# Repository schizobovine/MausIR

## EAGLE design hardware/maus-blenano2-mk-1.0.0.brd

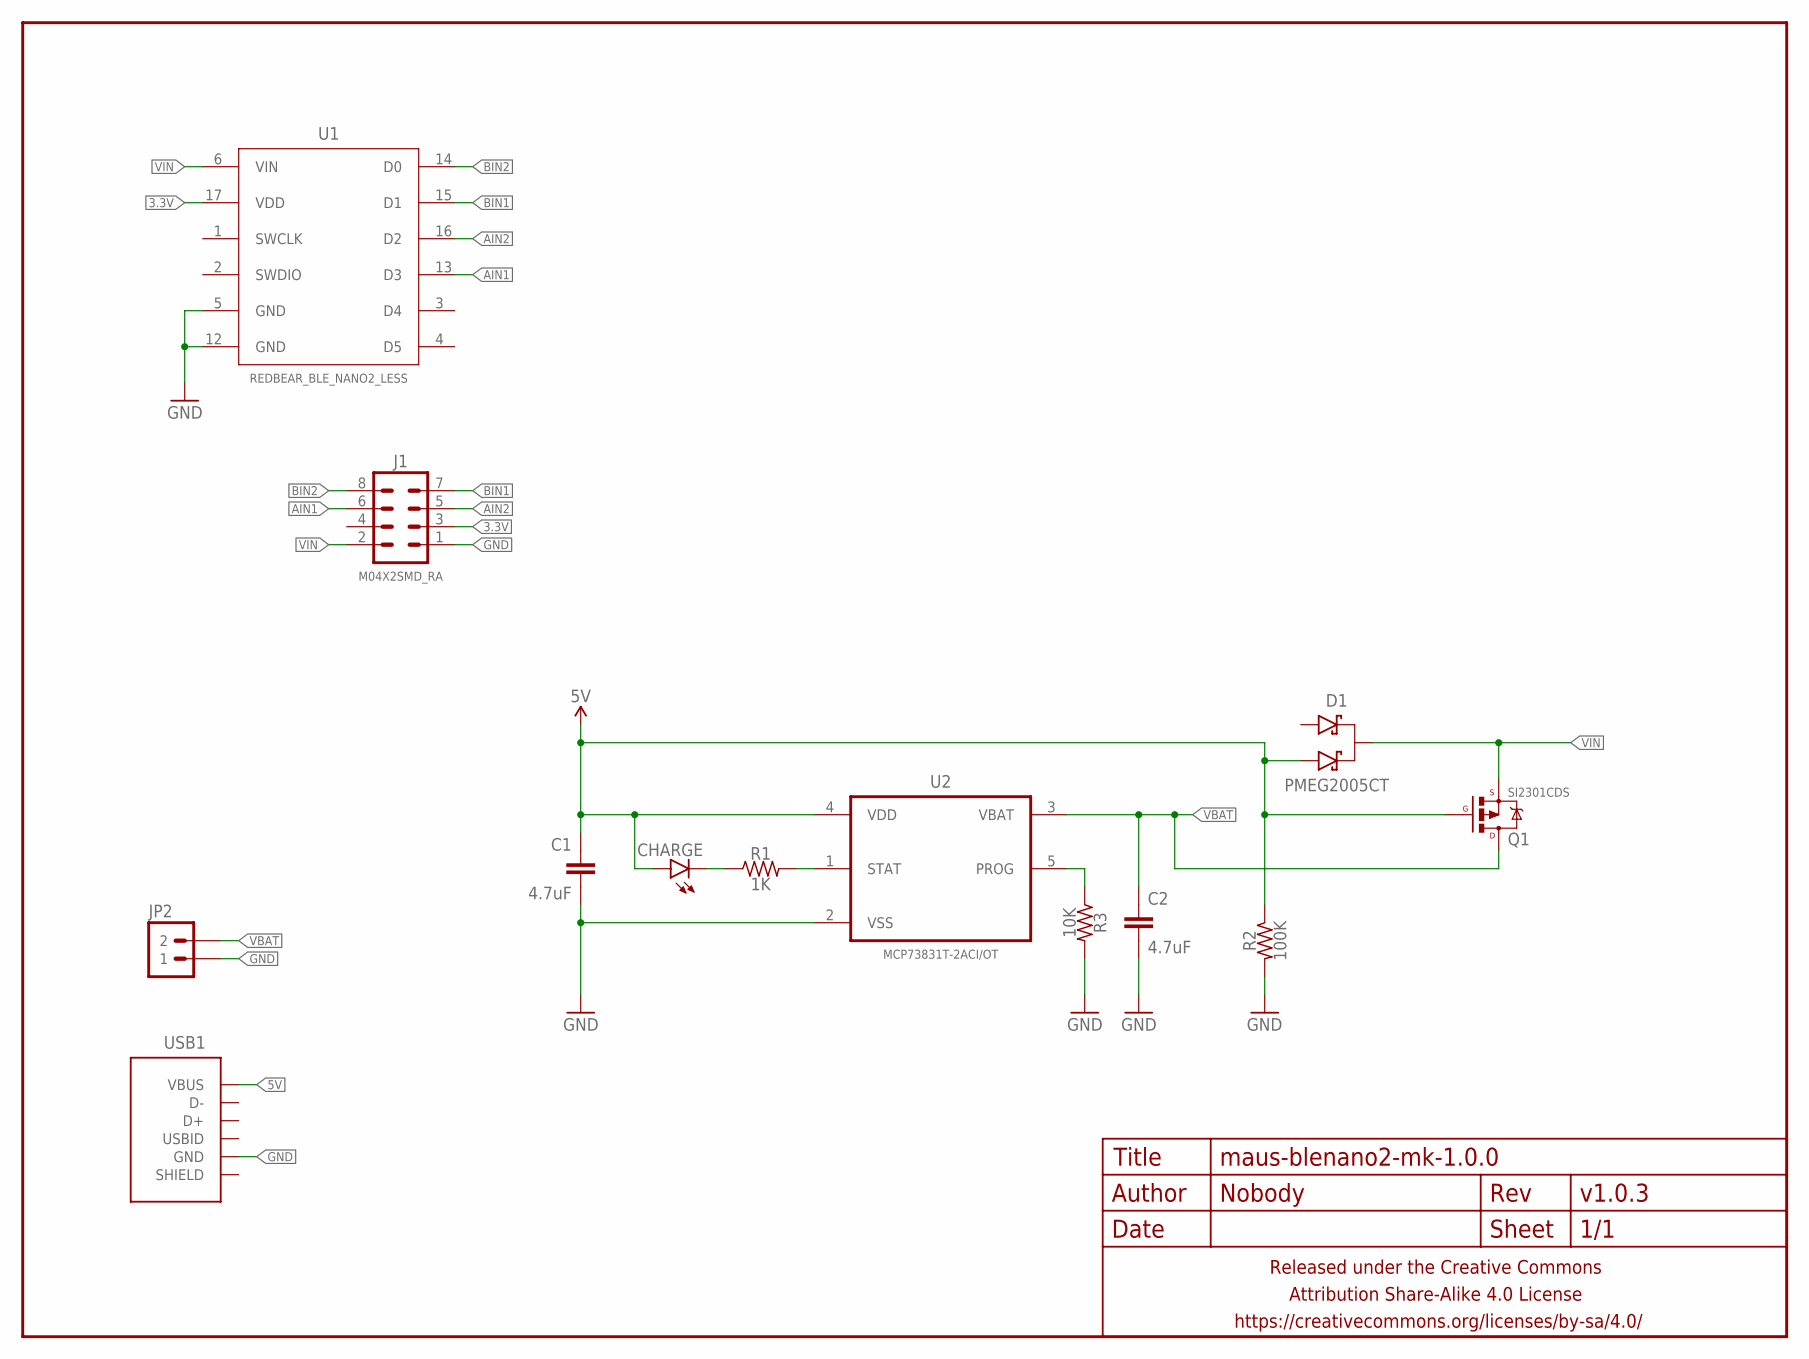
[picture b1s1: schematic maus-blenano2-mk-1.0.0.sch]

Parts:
C1, C2: 4.7uF; C0603-TIGHTER
CHARGE: LED0603-TIGHT; LED-0603-TIGHT
D1: PMEG2005CT; SOT23
FRAME1: FRAME-LETTERNO_PACKAGE; DUMMY
J1: M04X2SMD_RA; 2X4_SMD_RA
JP2: M02JST-SH-VERT; JST-2-SH-VERT
Q1: SI2301CDS; SOT23
R1: 1K; R0603-TIGHTER
R2: 100K; R0603-TIGHTER
R3: 10K; R0603-TIGHTER
U1: REDBEAR_BLE_NANO2_LESS
U2: MCP73831T-2ACI/OT; SOT95P280X145-5N
USB1: USB-AB-SHIELDZX80-B-5P_VERTICAL_SMD; ZX80-B-5P-30

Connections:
3.3V: J1.3, U1.17 (VDD)
5V: C1.1, CHARGE.A, D1.2 (A2), Q1.1 (G), R2.1, U2.4 (VDD), USB1.5 (VBUS)
AIN1: J1.6, U1.13 (D3)
AIN2: J1.5, U1.16 (D2)
BIN1: J1.7, U1.15 (D1)
BIN2: J1.8, U1.14 (D0)
GND: C1.2, C2.2, J1.1, JP2.1, R2.2, R3.2, U1.5 (GND), U1.12 (GND), U2.2 (VSS), USB1.1 (GND)
unnamed: R1.2, U2.1 (STAT)
unnamed: CHARGE.C, R1.1
unnamed: R3.1, U2.5 (PROG)
VBAT: C2.1, JP2.2, Q1.3 (D), U2.3 (VBAT)
VIN: D1.3 (K), J1.2, Q1.2 (S), U1.6 (VIN)

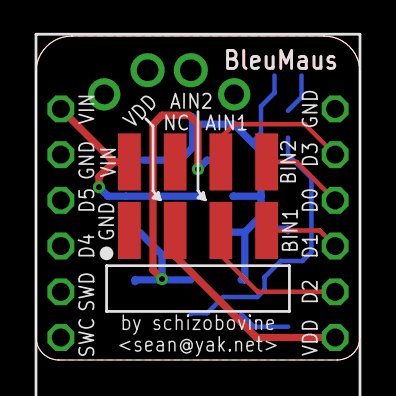
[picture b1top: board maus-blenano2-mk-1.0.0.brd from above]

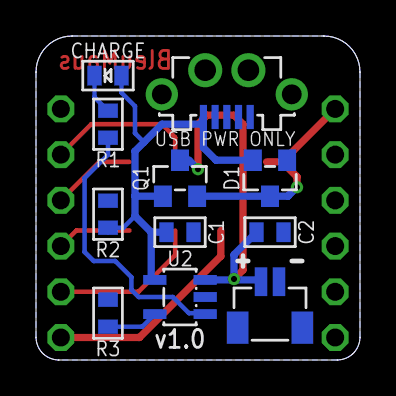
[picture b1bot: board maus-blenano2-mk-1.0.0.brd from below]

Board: 2 copper layers, 18.0 x 18.0 mm, 14 parts (11 on the bottom side), 12 nets.

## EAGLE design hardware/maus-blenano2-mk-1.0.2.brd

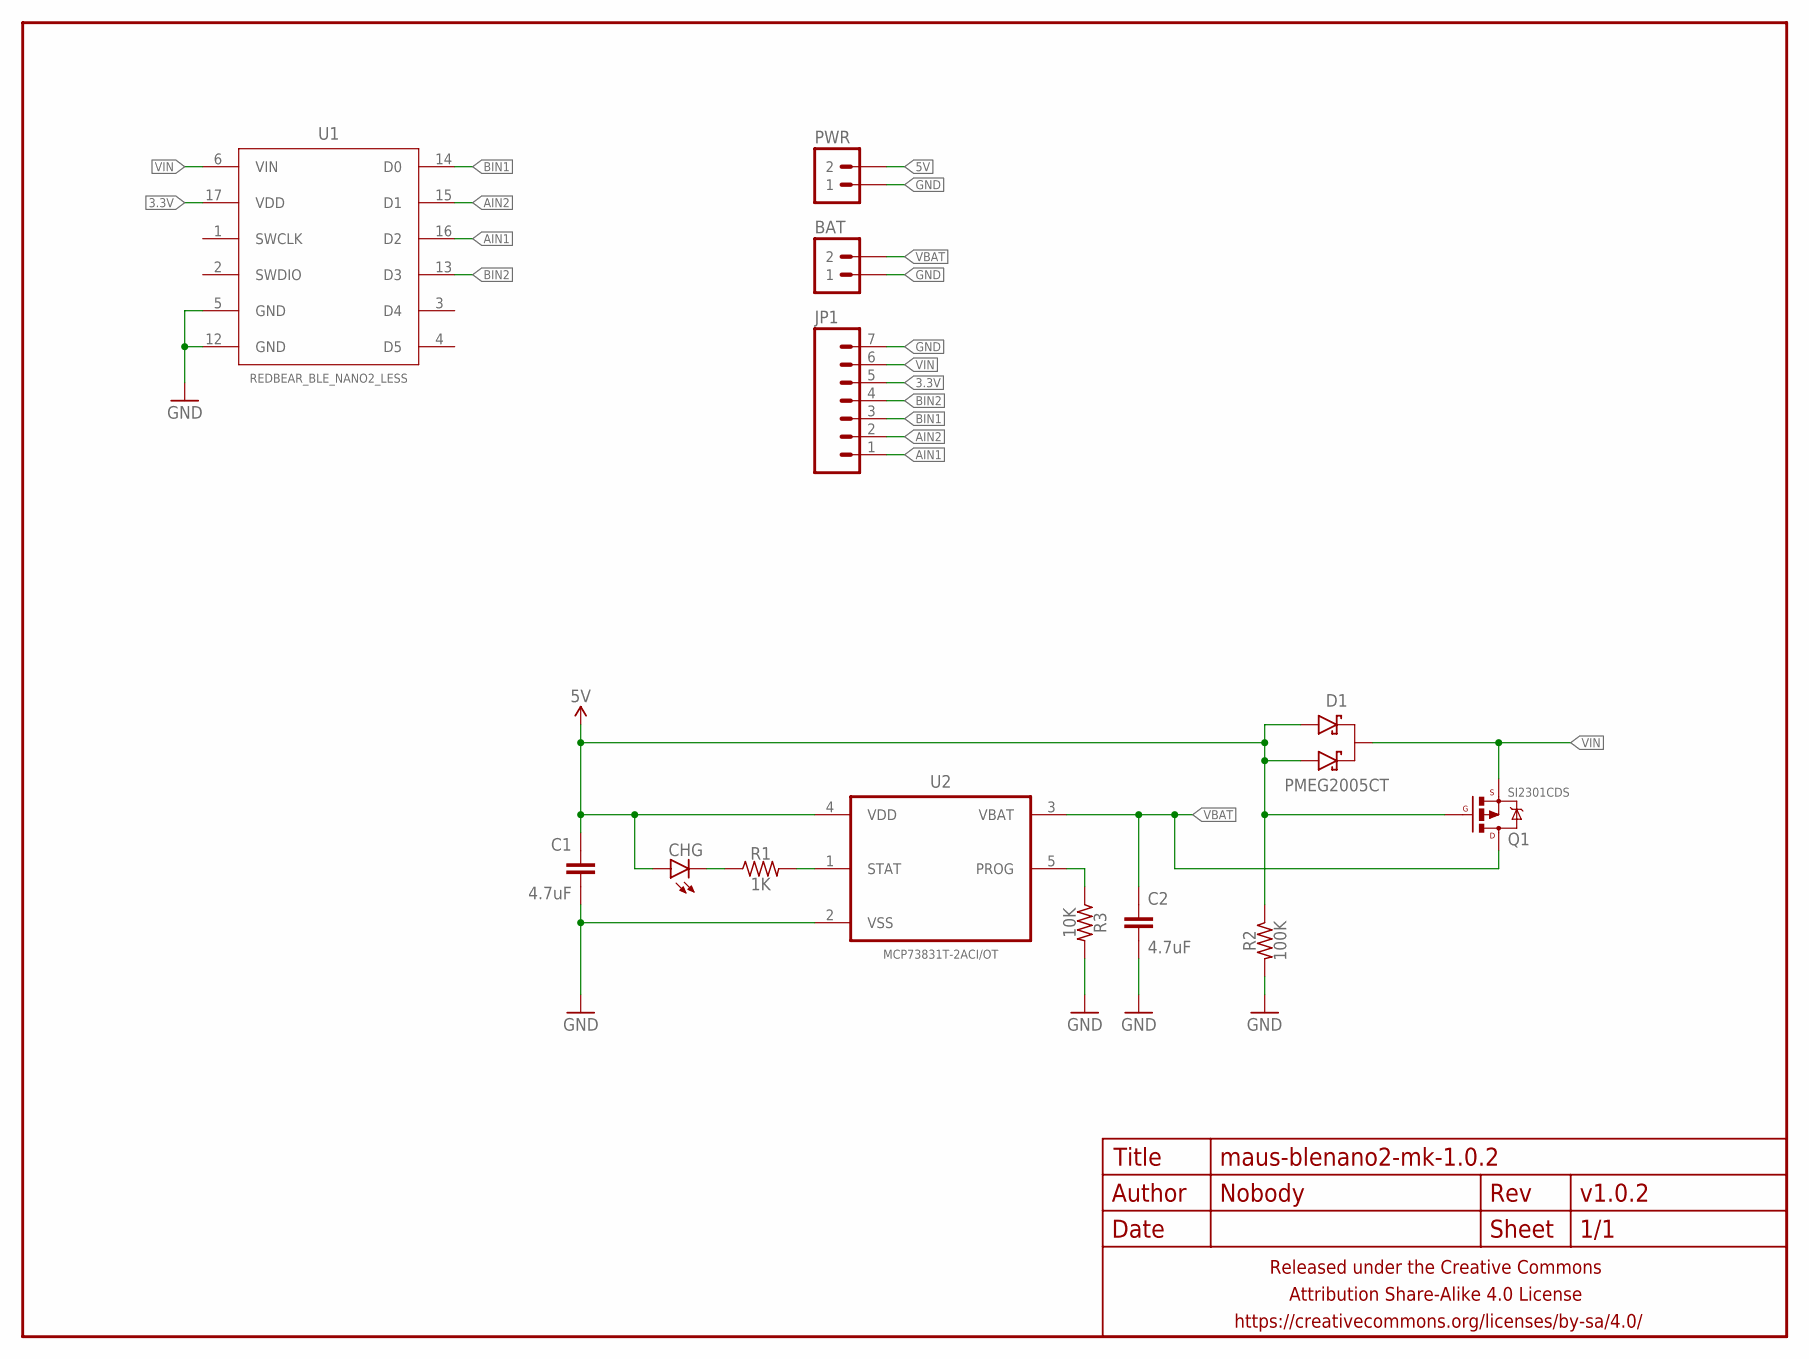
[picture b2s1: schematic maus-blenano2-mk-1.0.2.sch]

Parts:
BAT: M02JST-SH-RA; JST-2-SH-RA
C1, C2: 4.7uF; C0603-TIGHTER
CHG: LED0603-TIGHT; LED-0603-TIGHT
D1: PMEG2005CT; SOT23
FRAME1: FRAME-LETTERNO_PACKAGE; DUMMY
JP1: M07PTH-CENTERED; 1X07_CENTERED
PWR: M02JST-SH-RA; JST-2-SH-RA
Q1: SI2301CDS; SOT23
R1: 1K; R0603-TIGHTER
R2: 100K; R0603-TIGHTER
R3: 10K; R0603-TIGHTER
U1: REDBEAR_BLE_NANO2_LESS
U2: MCP73831T-2ACI/OT; SOT95P280X145-5N

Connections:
3.3V: JP1.5, U1.17 (VDD)
5V: C1.1, CHG.A, D1.1 (A1), D1.2 (A2), PWR.2, Q1.1 (G), R2.1, U2.4 (VDD)
AIN1: JP1.1, U1.16 (D2)
AIN2: JP1.2, U1.15 (D1)
BIN1: JP1.3, U1.14 (D0)
BIN2: JP1.4, U1.13 (D3)
GND: BAT.1, C1.2, C2.2, JP1.7, PWR.1, R2.2, R3.2, U1.5 (GND), U1.12 (GND), U2.2 (VSS)
unnamed: R1.2, U2.1 (STAT)
unnamed: CHG.C, R1.1
unnamed: R3.1, U2.5 (PROG)
VBAT: BAT.2, C2.1, Q1.3 (D), U2.3 (VBAT)
VIN: D1.3 (K), JP1.6, Q1.2 (S), U1.6 (VIN)

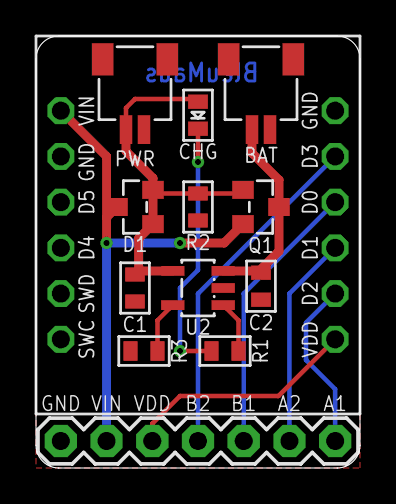
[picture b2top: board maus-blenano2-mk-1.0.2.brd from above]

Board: 2 copper layers, 18.0 x 24.0 mm, 14 parts (0 on the bottom side), 12 nets.

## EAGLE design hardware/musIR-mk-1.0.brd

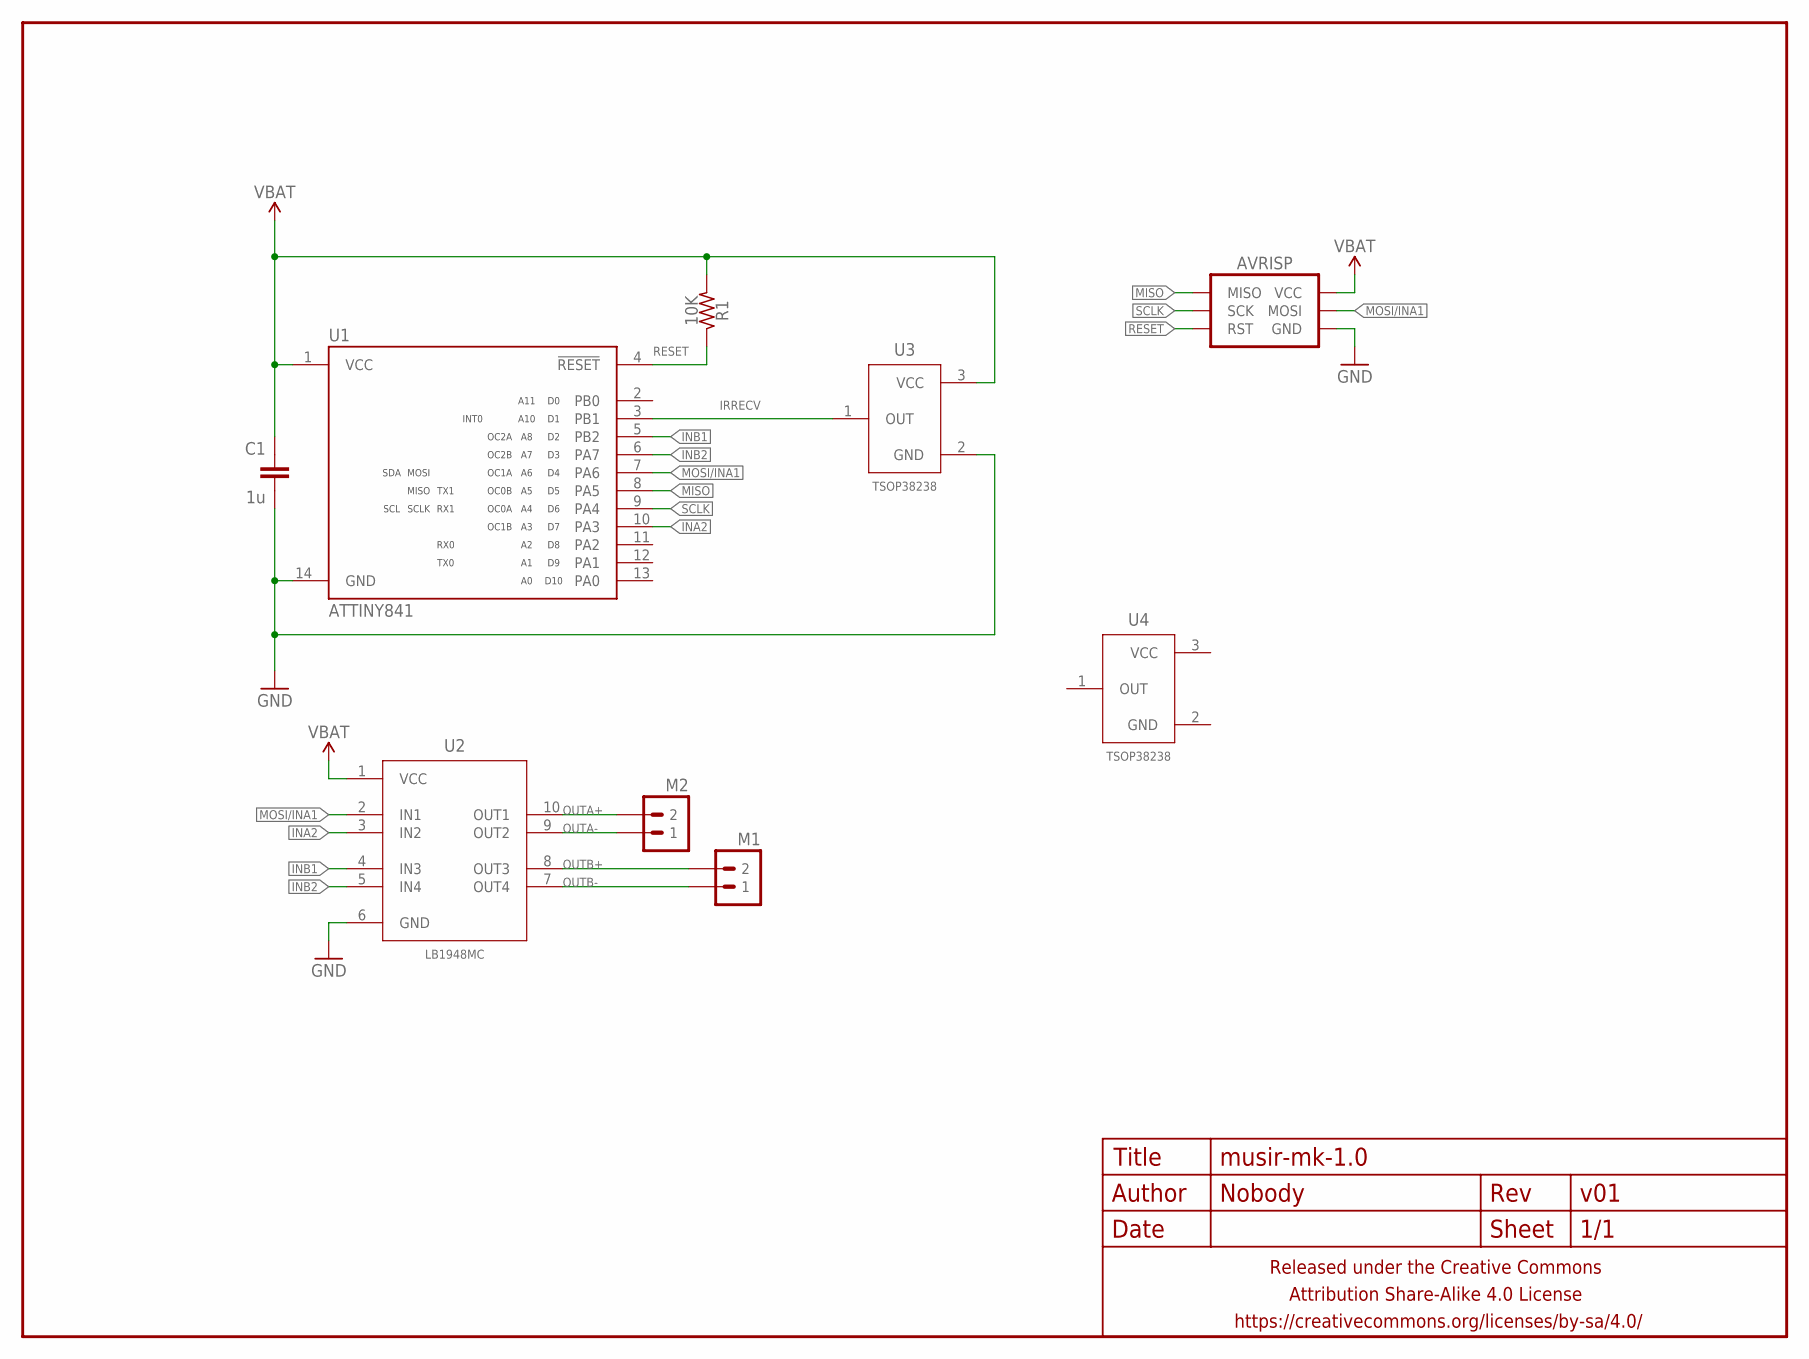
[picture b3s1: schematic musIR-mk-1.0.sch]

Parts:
AVRISP: AVR_SPI_PRG_6TESTPOINTS; 2X3_TEST_POINTS
C1: 1u; C0603-TIGHTER
FRAME1: FRAME-LETTERNO_PACKAGE; DUMMY
M1, M2: M02PTH; 1X02
R1: 10K; R0603-TIGHTER
U1: ATTINY841; SO14
U2: LB1948MC; SO10-NOTREALLY
U3, U4: TSOP38238

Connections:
GND: AVRISP.6 (GND), C1.2, U1.14 (GND), U2.6 (GND), U3.2 (GND)
INA2: U1.10 (PA3), U2.3 (IN2)
INB1: U1.5 (PB2), U2.4 (IN3)
INB2: U1.6 (PA7), U2.5 (IN4)
IRRECV: U1.3 (PB1), U3.1 (OUT)
MISO: AVRISP.1 (MISO), U1.8 (PA5)
MOSI/INA1: AVRISP.4 (MOSI), U1.7 (PA6), U2.2 (IN1)
OUTA+: M2.2, U2.10 (OUT1)
OUTA-: M2.1, U2.9 (OUT2)
OUTB+: M1.2, U2.8 (OUT3)
OUTB-: M1.1, U2.7 (OUT4)
RESET: AVRISP.5 (RST), R1.1, U1.4 (!RESET)
SCLK: AVRISP.3 (SCK), U1.9 (PA4)
VBAT: AVRISP.2 (VCC), C1.1, R1.2, U1.1 (VCC), U2.1 (VCC), U3.3 (VCC)

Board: 2 copper layers, 10 parts (1 on the bottom side), 14 nets, no tracks yet.

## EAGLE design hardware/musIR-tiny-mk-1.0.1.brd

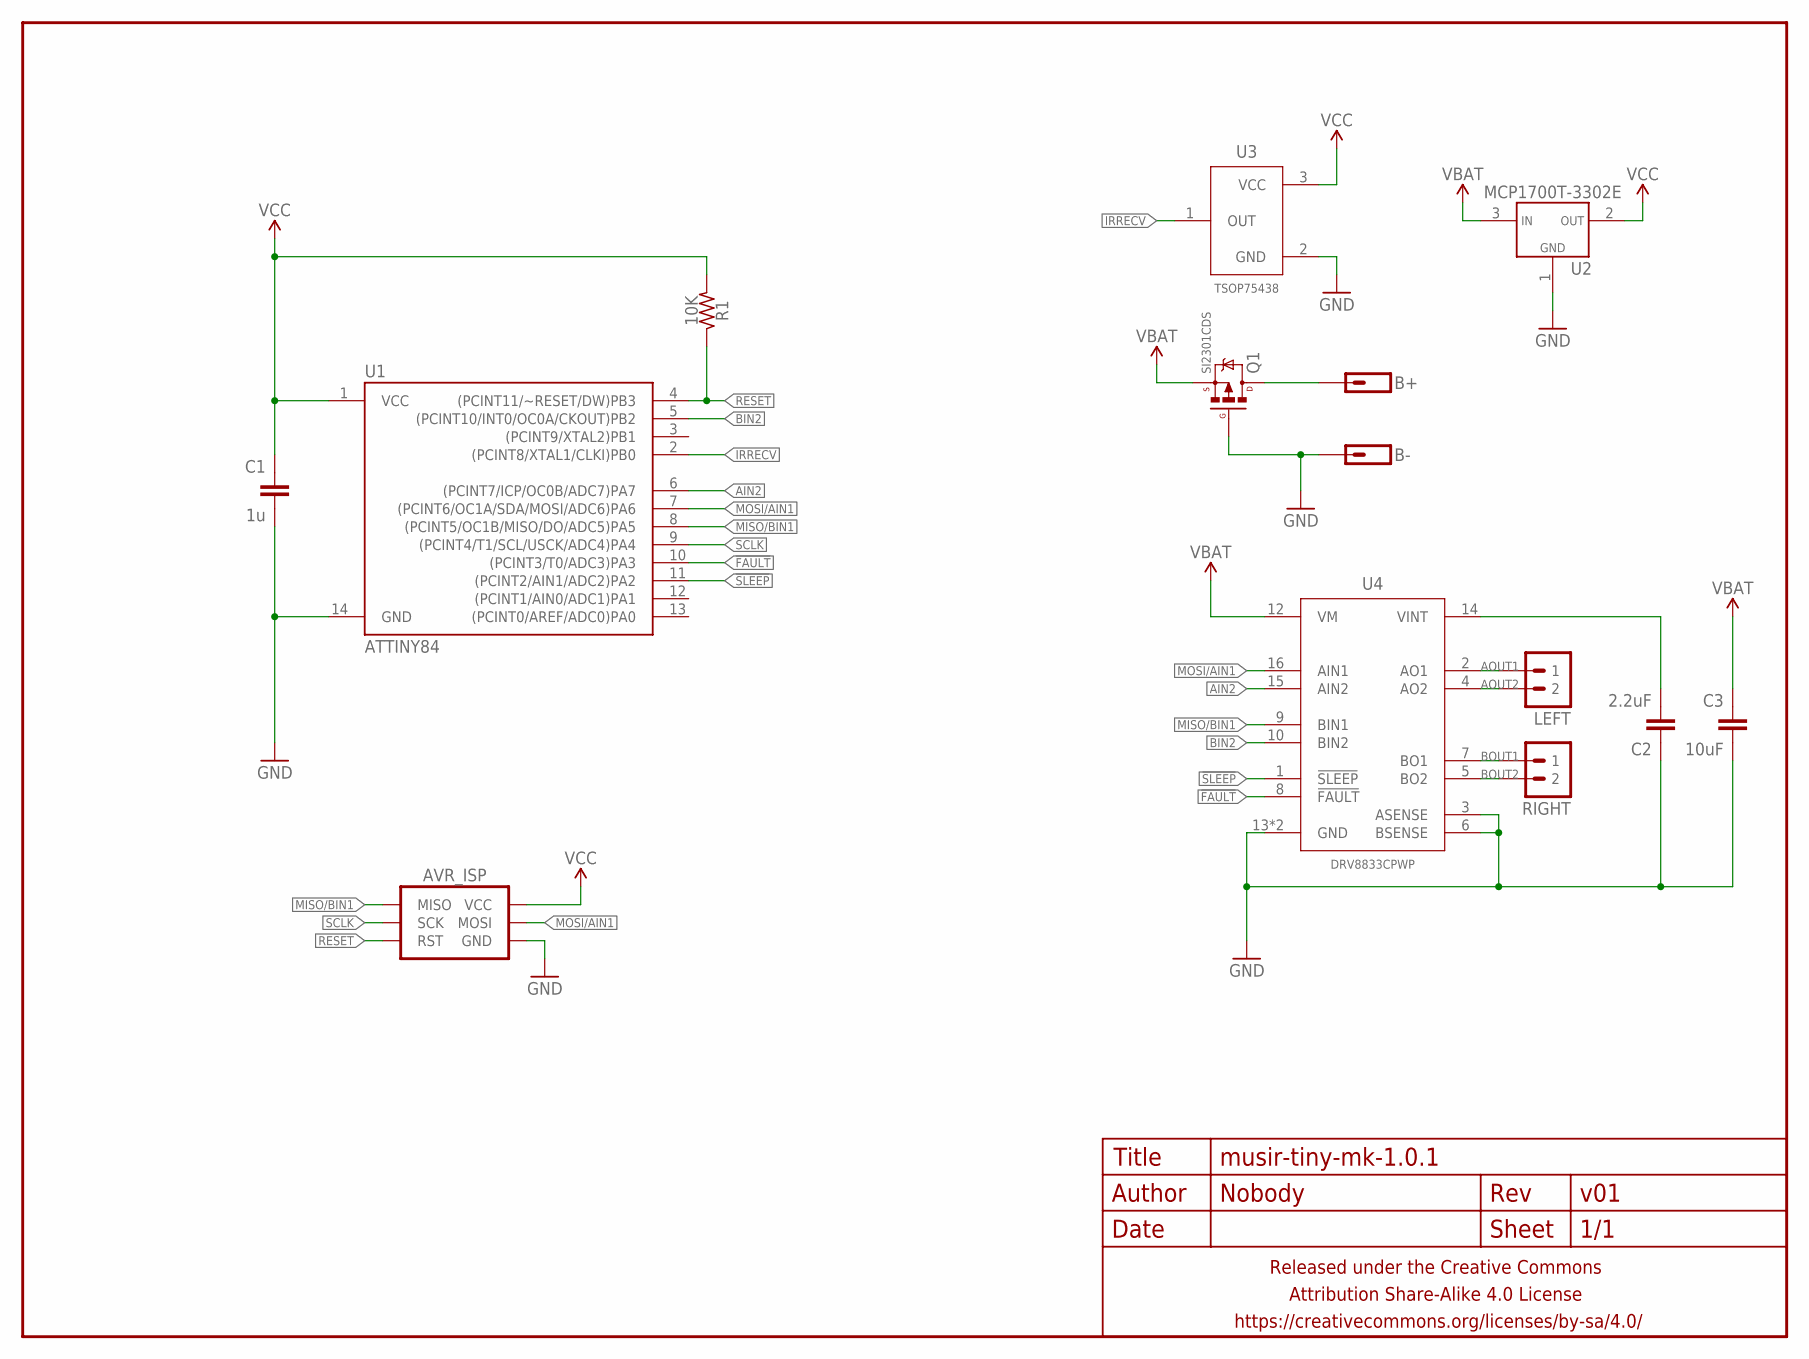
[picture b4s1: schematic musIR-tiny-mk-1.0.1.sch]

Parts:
AVR_ISP: AVR_SPI_PRG_6TESTPOINTS; 2X3_TEST_POINTS
B+: M01PTH; 1X01
B-: M01PTH; 1X01
C1: 1u; C0603-TIGHTER
C2: 2.2uF; C0603-TIGHTER
C3: 10uF; C0805-TIGHTER
FRAME1: FRAME-LETTERNO_PACKAGE; DUMMY
LEFT: M02PTH-CENTERED; 1X02-CENTER
Q1: SI2301CDS; SOT23
R1: 10K; R0402
RIGHT: M02PTH-CENTERED; 1X02-CENTER
U1: ATTINY84; SO14
U2: MCP1700T-3302E; SOT23-3
U3: TSOP75438; TSOP38238
U4: DRV8833CPWP; TSSOP-16-PAD

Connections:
!FAULT: U1.10 ((PCINT3/T0/ADC3)PA3), U4.8 (!FAULT)
!SLEEP: U1.11 ((PCINT2/AIN1/ADC2)PA2), U4.1 (!SLEEP)
AIN2: U1.6 ((PCINT7/ICP/OC0B/ADC7)PA7), U4.15 (AIN2)
AOUT1: LEFT.1, U4.2 (AO1)
AOUT2: LEFT.2, U4.4 (AO2)
BIN2: U1.5 ((PCINT10/INT0/OC0A/CKOUT)PB2), U4.10 (BIN2)
BOUT1: RIGHT.1, U4.7 (BO1)
BOUT2: RIGHT.2, U4.5 (BO2)
GND: AVR_ISP.6 (GND), B-.1, C1.2, C2.1, C3.2, Q1.1 (G), U1.14 (GND), U2.1 (GND), U3.2 (GND), U4.3 (ASENSE), U4.6 (BSENSE), U4.13 (GND), U4.PAD (GND)
IRRECV: U1.2 ((PCINT8/XTAL1/CLKI)PB0), U3.1 (OUT)
MISO/BIN1: AVR_ISP.1 (MISO), U1.8 ((PCINT5/OC1B/MISO/DO/ADC5)PA5), U4.9 (BIN1)
MOSI/AIN1: AVR_ISP.4 (MOSI), U1.7 ((PCINT6/OC1A/SDA/MOSI/ADC6)PA6), U4.16 (AIN1)
unnamed: B+.1, Q1.3 (D)
unnamed: C2.2, U4.14 (VINT)
RESET: AVR_ISP.5 (RST), R1.1, U1.4 ((PCINT11/~RESET/DW)PB3)
SCLK: AVR_ISP.3 (SCK), U1.9 ((PCINT4/T1/SCL/USCK/ADC4)PA4)
VBAT: C3.1, Q1.2 (S), U2.3 (VIN), U4.12 (VM)
VCC: AVR_ISP.2 (VCC), C1.1, R1.2, U1.1 (VCC), U2.2 (VOUT), U3.3 (VCC)

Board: 2 copper layers, 15 parts (4 on the bottom side), 18 nets, no tracks yet.

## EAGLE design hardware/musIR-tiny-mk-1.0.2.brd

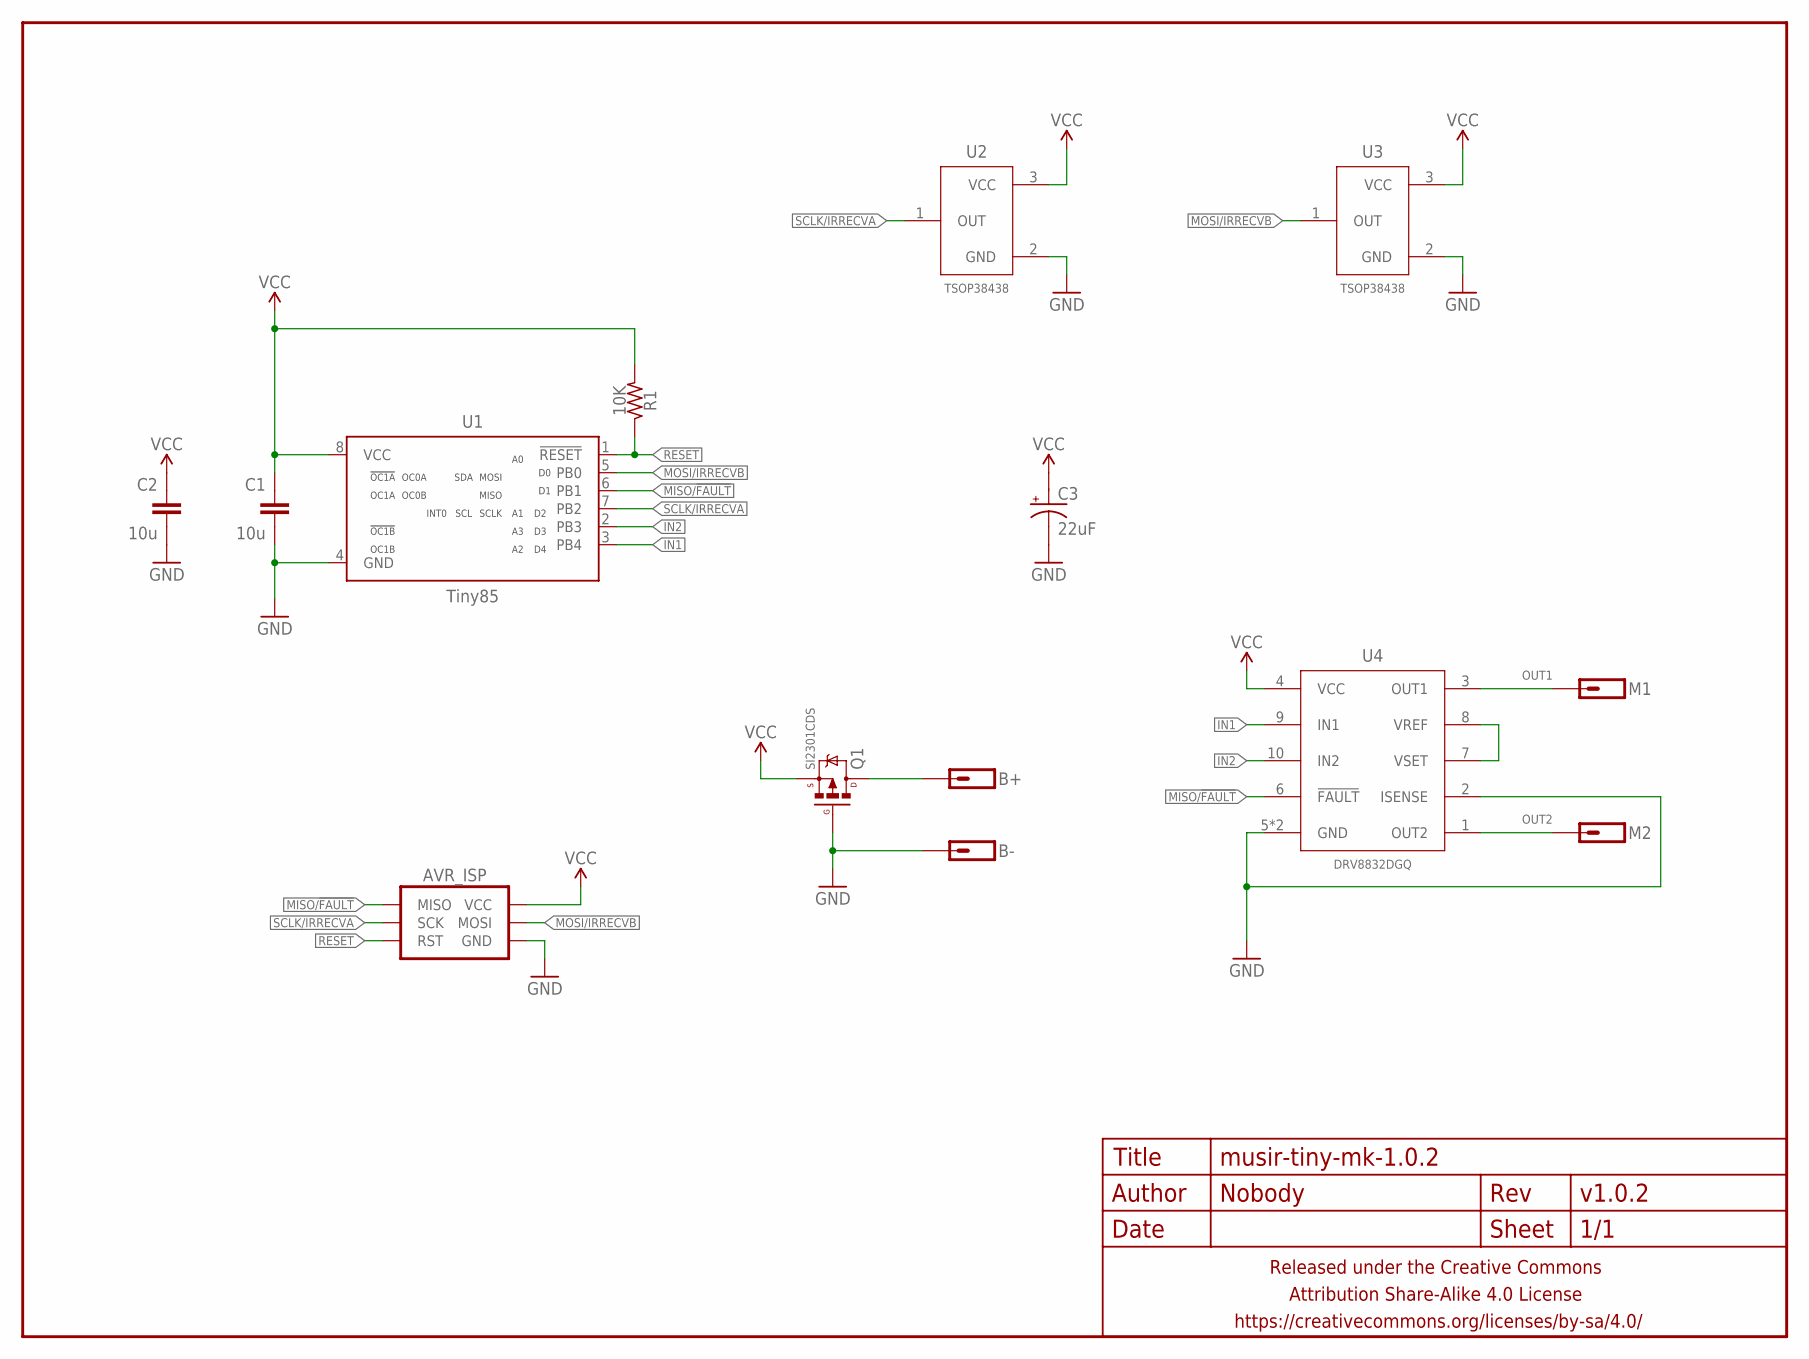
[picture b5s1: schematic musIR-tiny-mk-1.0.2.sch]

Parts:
AVR_ISP: AVR_SPI_PRG_6TESTPOINTS; 2X3_TEST_POINTS
B+: M01PTH; 1X01
B-: M01PTH; 1X01
C1, C2: 10u; C0805-TIGHTER
C3: 22uF; C/6032-28R
FRAME1: FRAME-LETTERNO_PACKAGE; DUMMY
M1, M2: M01PTH; 1X01
Q1: SI2301CDS; SOT23
R1: 10K; R0603-TIGHTER
U1: Tiny85; SO08-EIAJ
U2, U3: TSOP38438; TSOP38238
U4: DRV8832DGQ; MSOP-10-PAD

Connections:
GND: AVR_ISP.6 (GND), B-.1, C1.2, C2.2, C3.-, Q1.1 (G), U1.4 (GND), U2.2 (GND), U3.2 (GND), U4.2 (ISENSE), U4.5 (GND), U4.PAD (GND)
IN1: U1.3 (PB4), U4.9 (IN1)
IN2: U1.2 (PB3), U4.10 (IN2)
MISO/!FAULT: AVR_ISP.1 (MISO), U1.6 (PB1), U4.6 (!FAULT)
MOSI/IRRECVB: AVR_ISP.4 (MOSI), U1.5 (PB0), U3.1 (OUT)
unnamed: B+.1, Q1.3 (D)
unnamed: U4.7 (VSET), U4.8 (VREF)
OUT1: M1.1, U4.3 (OUT1)
OUT2: M2.1, U4.1 (OUT2)
RESET: AVR_ISP.5 (RST), R1.1, U1.1 (!RESET)
SCLK/IRRECVA: AVR_ISP.3 (SCK), U1.7 (PB2), U2.1 (OUT)
VCC: AVR_ISP.2 (VCC), C1.1, C2.1, C3.+, Q1.2 (S), R1.2, U1.8 (VCC), U2.3 (VCC), U3.3 (VCC), U4.4 (VCC)

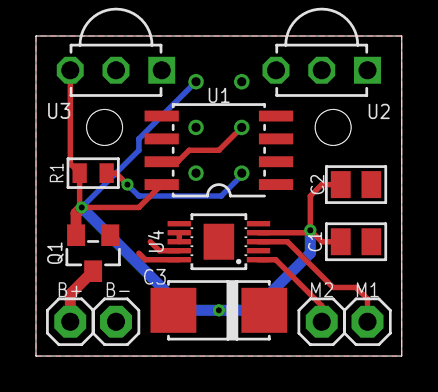
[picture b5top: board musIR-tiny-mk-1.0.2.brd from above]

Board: 2 copper layers, 20.3 x 17.8 mm, 15 parts (1 on the bottom side), 12 nets.

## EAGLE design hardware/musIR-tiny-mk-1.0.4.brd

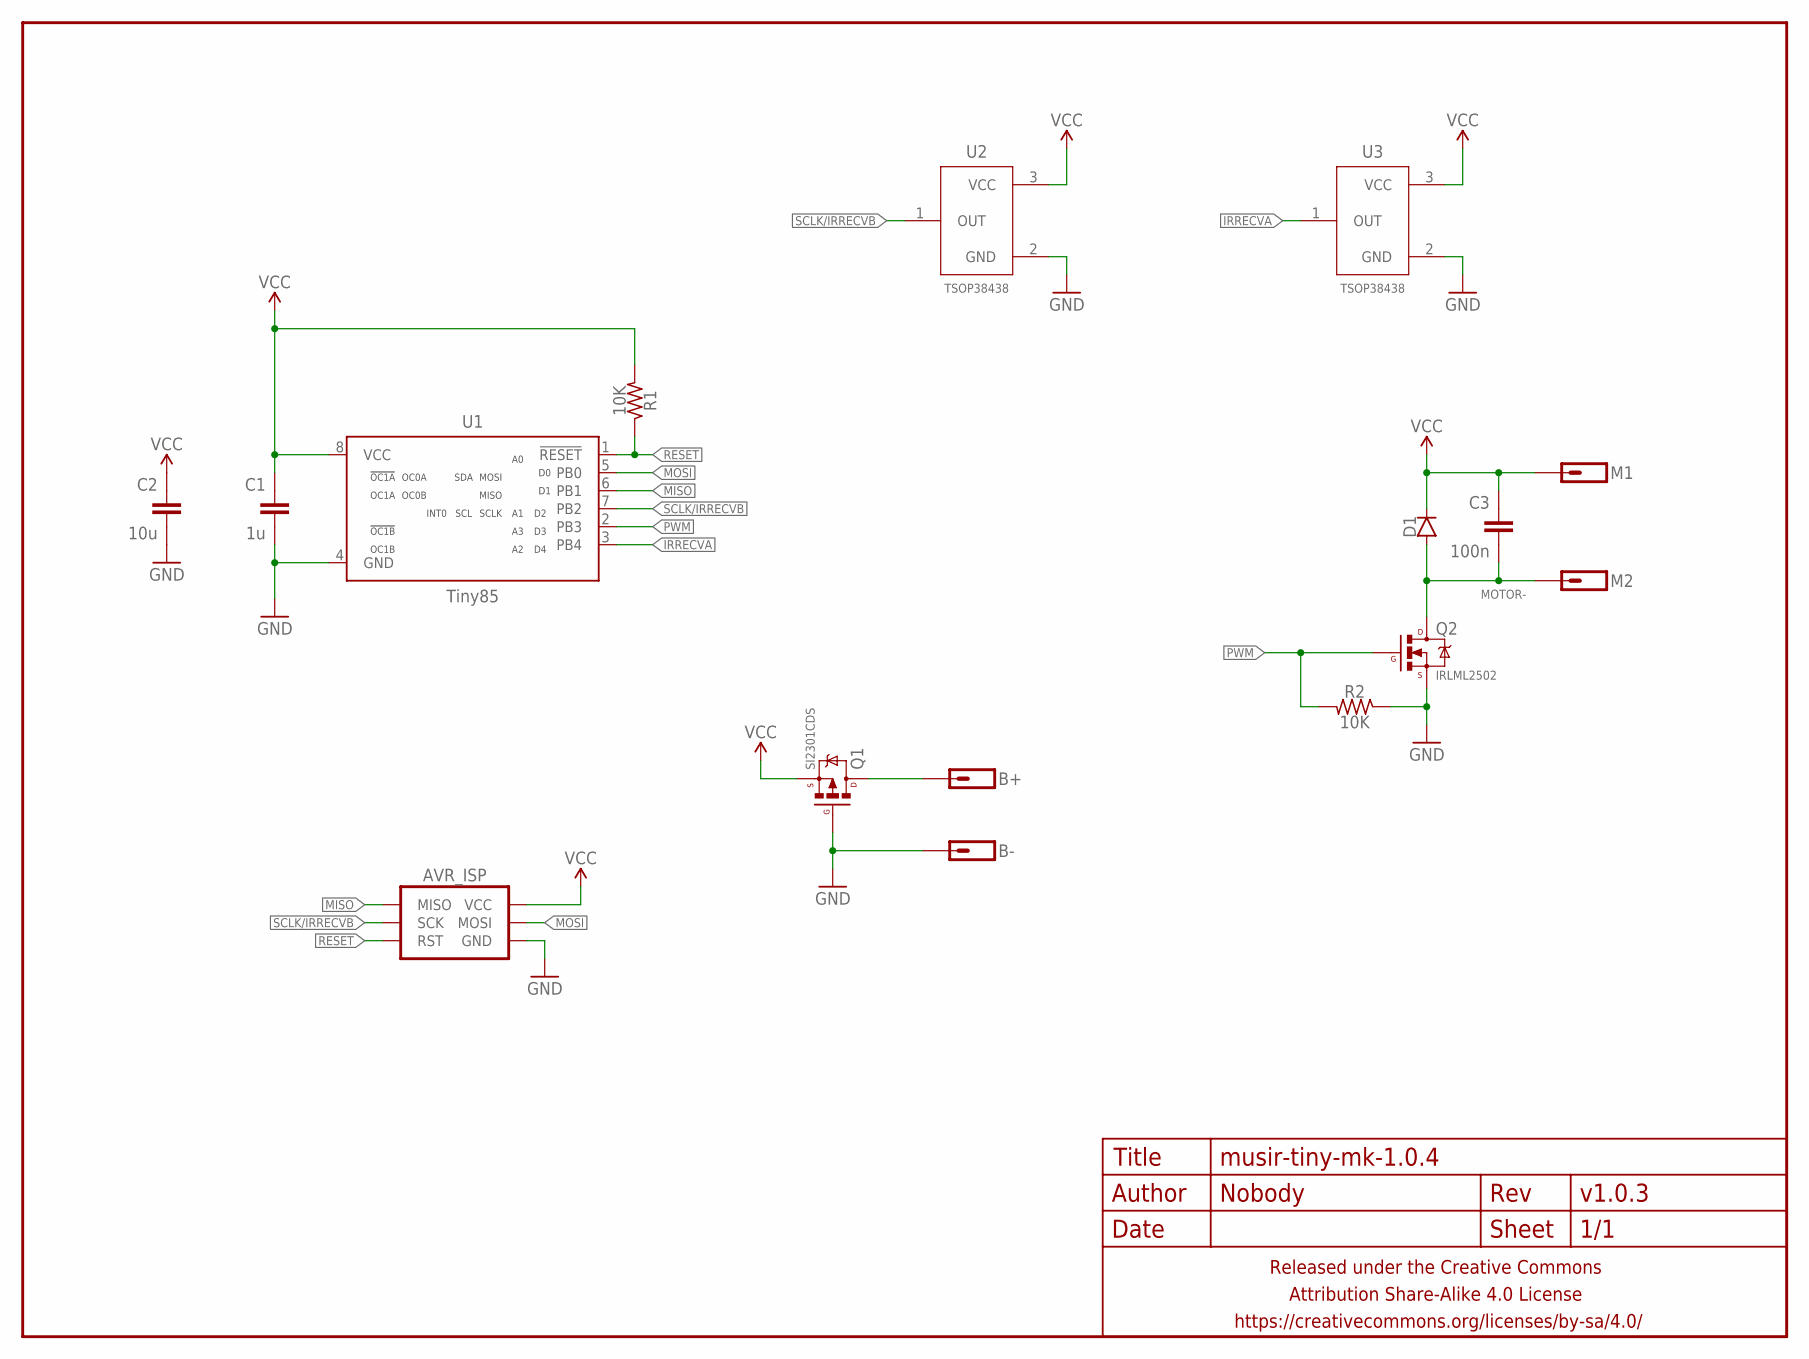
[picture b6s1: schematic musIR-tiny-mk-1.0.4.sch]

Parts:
AVR_ISP: AVR_SPI_PRG_6TESTPOINTS; 2X3_TEST_POINTS
B+: M01PTH; 1X01
B-: M01PTH; 1X01
C1: 1u; C0603-TIGHTER
C2: 10u; C0805-TIGHTER
C3: 100n; C0603-TIGHTER
D1: DIODESOD123; SOD123
FRAME1: FRAME-LETTERNO_PACKAGE; DUMMY
M1, M2: M01PTH; 1X01
Q1: SI2301CDS; SOT23
Q2: IRLML2502; SOT23
R1, R2: 10K; R0603-TIGHTER
U1: Tiny85; SO08-EIAJ
U2, U3: TSOP38438; TSOP38238

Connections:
GND: AVR_ISP.6 (GND), B-.1, C1.2, C2.2, Q1.1 (G), Q2.2 (S), R2.1, U1.4 (GND), U2.2 (GND), U3.2 (GND)
IRRECVA: U1.3 (PB4), U3.1 (OUT)
MISO: AVR_ISP.1 (MISO), U1.6 (PB1)
MOSI: AVR_ISP.4 (MOSI), U1.5 (PB0)
MOTOR-: C3.2, D1.A, M2.1, Q2.3 (D)
unnamed: B+.1, Q1.3 (D)
PWM: Q2.1 (G), R2.2, U1.2 (PB3)
RESET: AVR_ISP.5 (RST), R1.1, U1.1 (!RESET)
SCLK/IRRECVB: AVR_ISP.3 (SCK), U1.7 (PB2), U2.1 (OUT)
VCC: AVR_ISP.2 (VCC), C1.1, C2.1, C3.1, D1.C, M1.1, Q1.2 (S), R1.2, U1.8 (VCC), U2.3 (VCC), U3.3 (VCC)

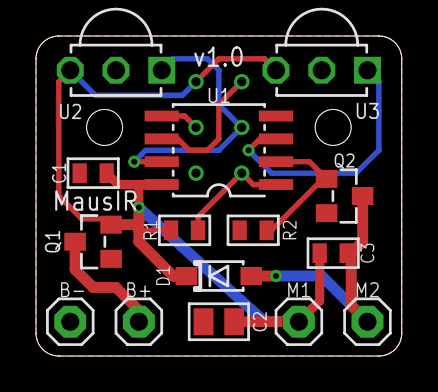
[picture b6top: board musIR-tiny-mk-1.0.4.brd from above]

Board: 2 copper layers, 20.3 x 17.8 mm, 17 parts (1 on the bottom side), 10 nets.

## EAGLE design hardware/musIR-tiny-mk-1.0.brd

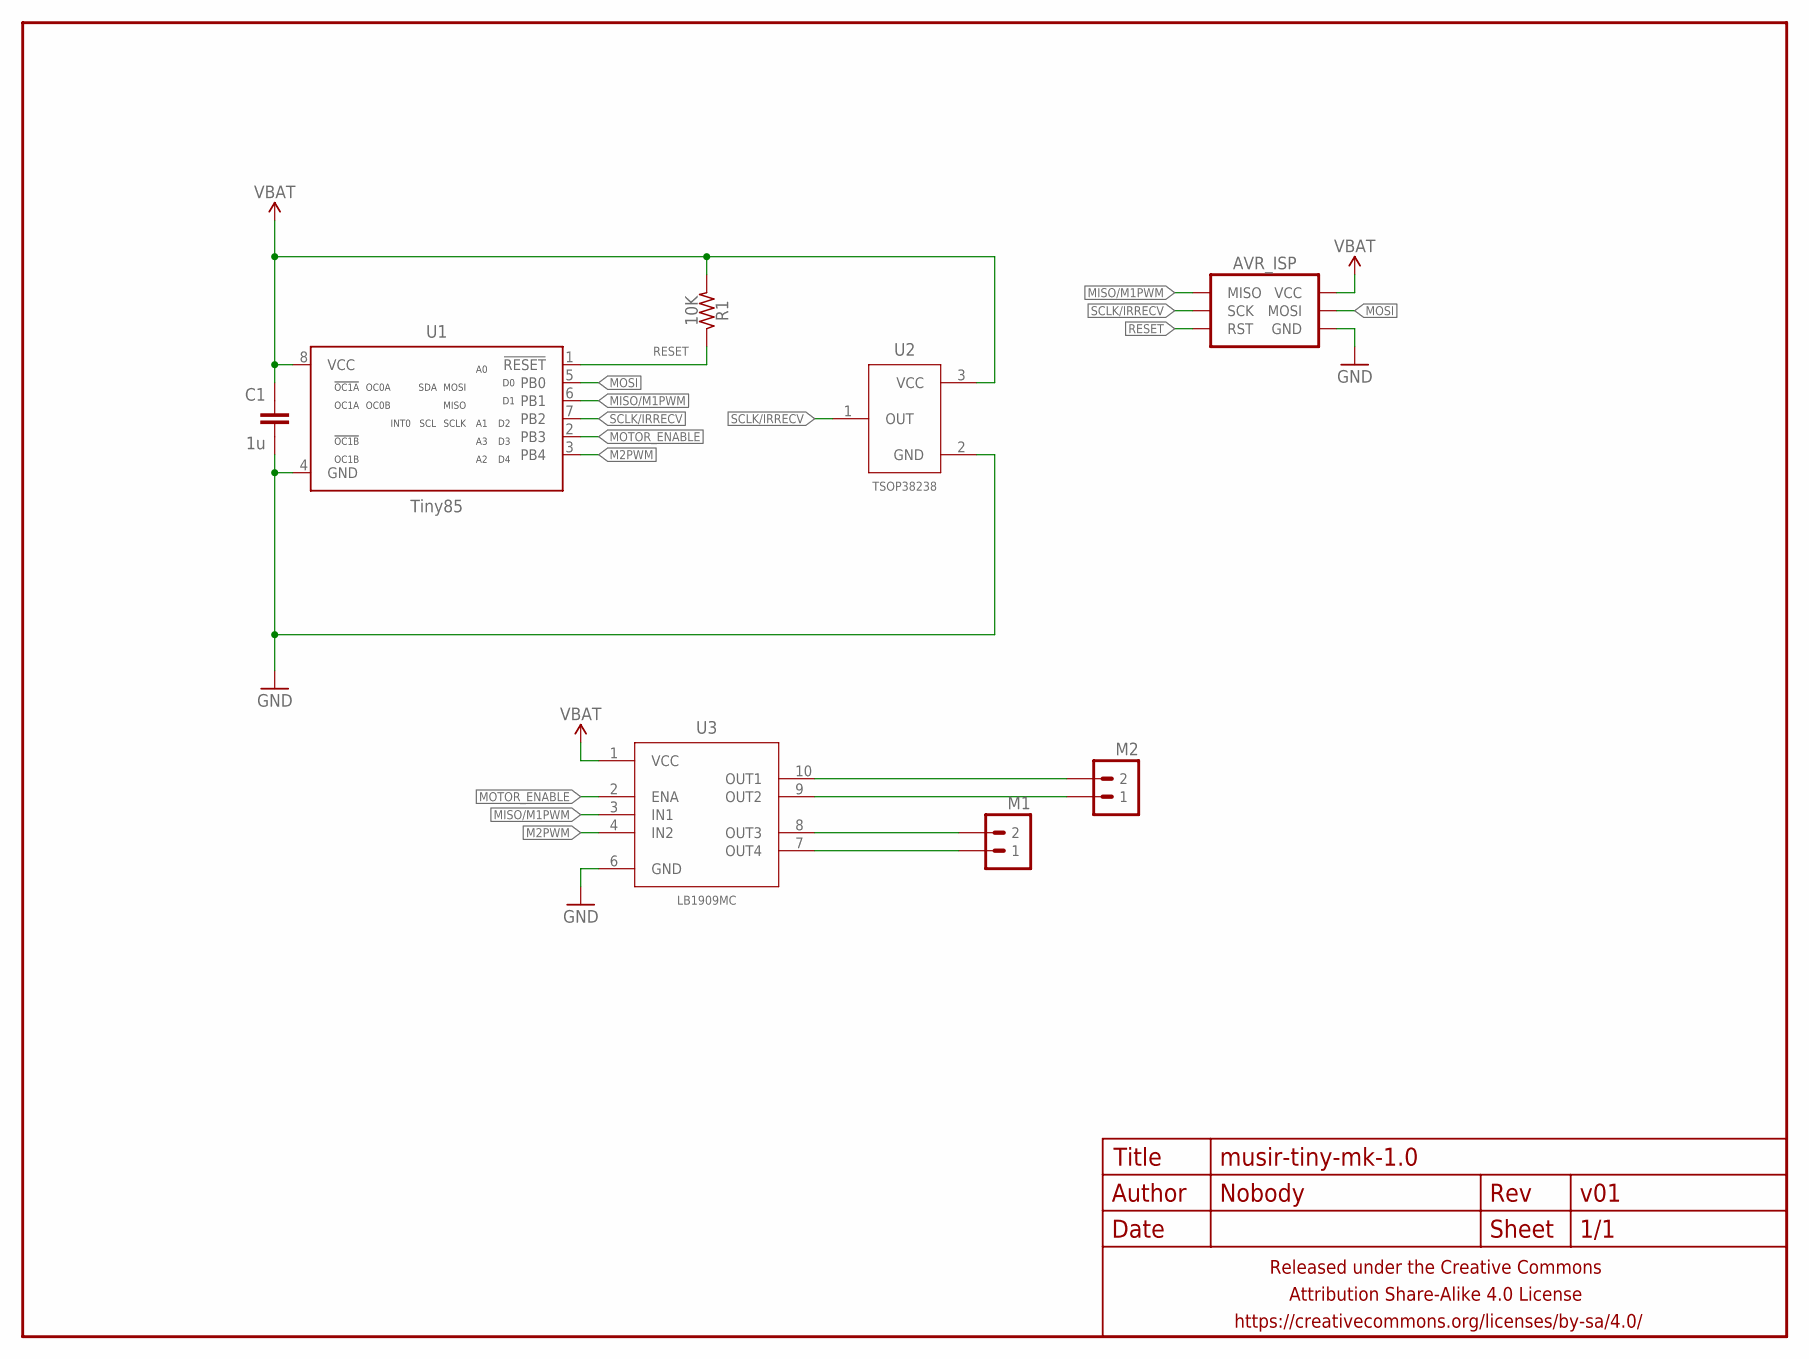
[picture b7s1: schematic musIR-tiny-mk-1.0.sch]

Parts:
AVR_ISP: AVR_SPI_PRG_6TESTPOINTS; 2X3_TEST_POINTS
C1: 1u; C0603-TIGHTER
FRAME1: FRAME-LETTERNO_PACKAGE; DUMMY
M1, M2: M02PTH-CENTERED; 1X02-CENTER
R1: 10K; R0603-TIGHTER
U1: Tiny85; SO08-EIAJ
U2: TSOP38238
U3: LB1909MC; SO10-NOTREALLY

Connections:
GND: AVR_ISP.6 (GND), C1.2, U1.4 (GND), U2.2 (GND), U3.6 (GND)
M2PWM: U1.3 (PB4), U3.4 (IN2)
MISO/M1PWM: AVR_ISP.1 (MISO), U1.6 (PB1), U3.3 (IN1)
MOSI: AVR_ISP.4 (MOSI), U1.5 (PB0)
MOTOR_ENABLE: U1.2 (PB3), U3.2 (ENA)
unnamed: M1.1, U3.7 (OUT4)
unnamed: M1.2, U3.8 (OUT3)
unnamed: M2.1, U3.9 (OUT2)
unnamed: M2.2, U3.10 (OUT1)
RESET: AVR_ISP.5 (RST), R1.1, U1.1 (!RESET)
SCLK/IRRECV: AVR_ISP.3 (SCK), U1.7 (PB2), U2.1 (OUT)
VBAT: AVR_ISP.2 (VCC), C1.1, R1.2, U1.8 (VCC), U2.3 (VCC), U3.1 (VCC)

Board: 2 copper layers, 9 parts (1 on the bottom side), 12 nets, no tracks yet.

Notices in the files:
parts and their libraries:
a_parts: Released under the Creative Commons Attribution Share-Alike 4.0 License
a_parts: https://creativecommons.org/licenses/by-sa/4.0
a_parts: Released under the Creative Commons
